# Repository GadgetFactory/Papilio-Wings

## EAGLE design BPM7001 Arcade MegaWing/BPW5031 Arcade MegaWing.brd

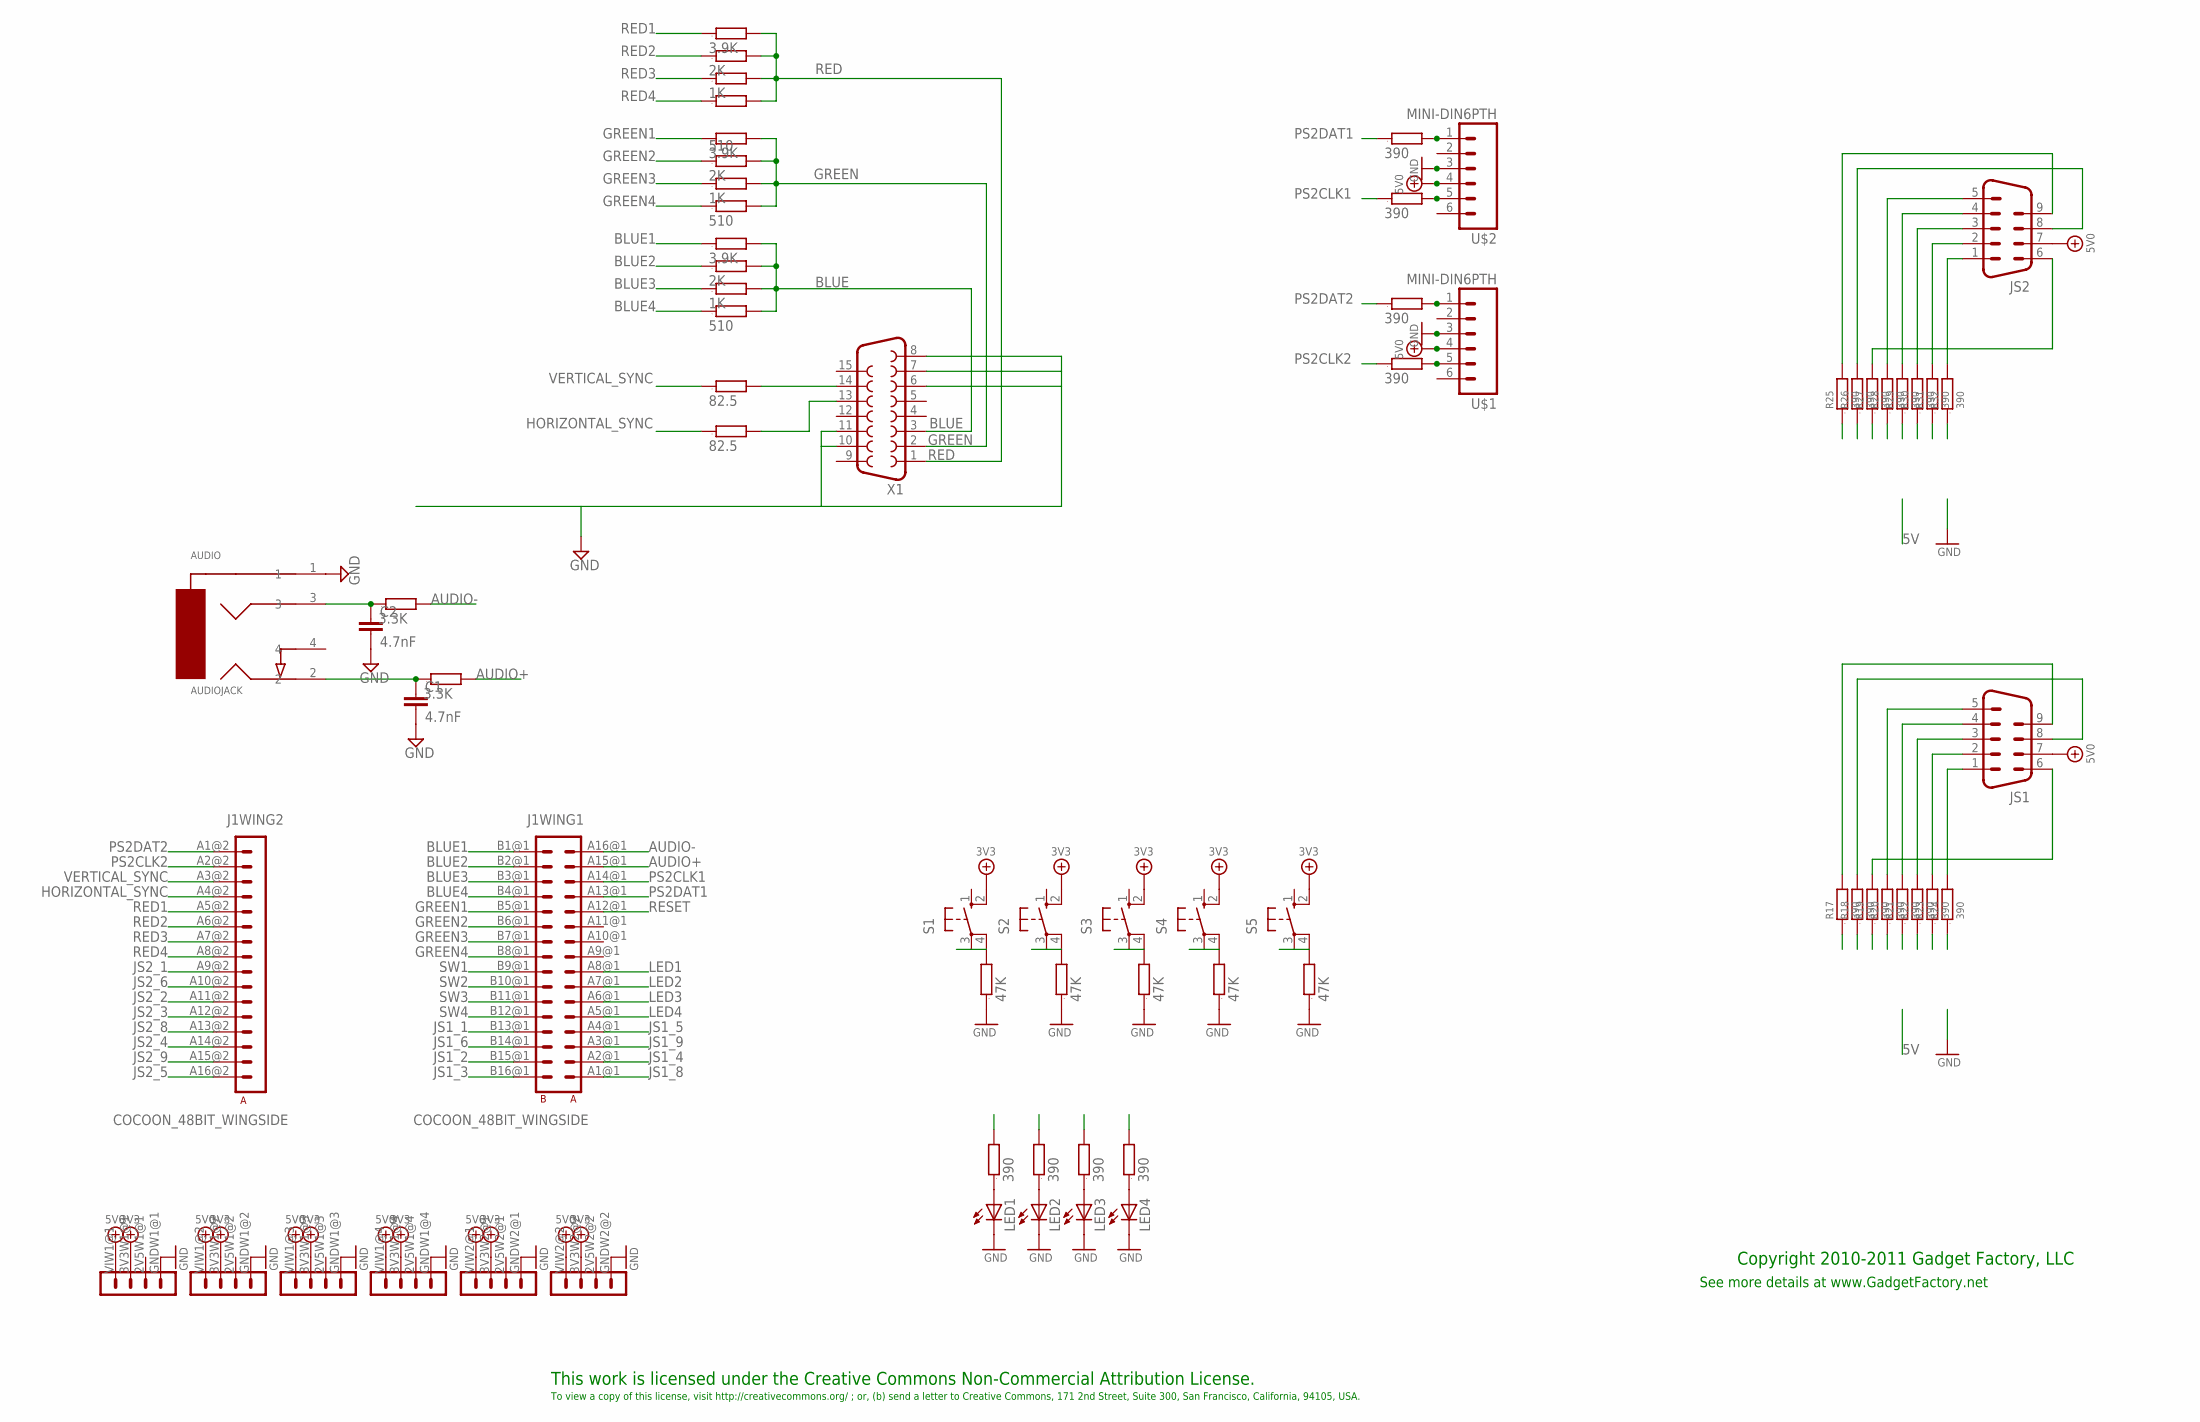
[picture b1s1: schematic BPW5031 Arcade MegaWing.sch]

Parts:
AUDIO: AUDIOJACK; AUDJCK
C1, C2: 4.7nF; C050-025X075
J1: COCOON_48BIT_WINGSIDE
JS1, JS2: M09HP
LED1, LED2, LED3, LED4: LEDCHIPLED_0603; CHIPLED_0603
LOGO2: BUTTERFLY_LOGO
R1, R2, R3: 3.9K; 0603
R4, R5: 82.5; 0603
R6, R7, R8: 2K; 0603
R9, R11, R13: 1K; 0603
R10, R12, R14: 510; 0603
R15, R16: 3.3K; 0603
R17, R18, R19, R20, R21, R22, R23, R24, R25, R26, R27, R28, R29, R30, R31, R32, R37, R38, R39, R40, R42, R43, R44, R45: 390; 0603
R33, R34, R35, R36, R41: 47K; 0603
S1, S2, S3, S4, S5: 10-XX; B3F-10XX
U$1, U$2: MINI-DIN6PTH; MINI-DIN6
X1: F15HDH; HDF15H

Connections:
3V3: J1.3V3W1@1 (3V3), J1.3V3W1@2 (3V3), J1.3V3W1@3 (3V3), J1.3V3W1@4 (3V3), J1.3V3W2@1 (3V3), J1.3V3W2@2 (3V3), S1.2 (S1), S2.2 (S1), S3.2 (S1), S4.2 (S1), S5.2 (S1)
5V0: J1.VIW1@1 (5V), J1.VIW1@2 (5V), J1.VIW1@3 (5V), J1.VIW1@4 (5V), J1.VIW2@1 (5V), J1.VIW2@2 (5V), JS1.7, JS2.7, U$1.4, U$2.4
AUDIO+: J1.A15@1 (A15), R16.2
AUDIO-: J1.A16@1 (A16), R15.2
BLUE: R3.2, R8.2, R13.2, R14.2, X1.3
BLUE1: J1.B1@1 (B1), R3.1
BLUE2: J1.B2@1 (B2), R8.1
BLUE3: J1.B3@1 (B3), R13.1
BLUE4: J1.B4@1 (B4), R14.1
GND: AUDIO.1, C1.2, C2.2, J1.GNDW1@1 (GND), J1.GNDW1@2 (GND), J1.GNDW1@3 (GND), J1.GNDW1@4 (GND), J1.GNDW2@1 (GND), J1.GNDW2@2 (GND), LED1.C, LED2.C, LED3.C, LED4.C, R33.1, R34.1, R35.1, R36.1, R41.1, U$1.3, U$2.3, X1.6, X1.7, X1.8, X1.10, X1.11
GREEN: R2.2, R7.2, R11.2, R12.2, X1.2
GREEN1: J1.B5@1 (B5), R2.1
GREEN2: J1.B6@1 (B6), R7.1
GREEN3: J1.B7@1 (B7), R11.1
GREEN4: J1.B8@1 (B8), R12.1
HORIZONTAL_SYNC: J1.A4@2 (A4), R4.1
JS1_1: J1.B13@1 (B13), R32.1
JS1_2: J1.B15@1 (B15), R31.1
JS1_3: J1.B16@1 (B16), R30.1
JS1_4: J1.A2@1 (A2), R29.1
JS1_5: J1.A4@1 (A4), R28.1
JS1_6: J1.B14@1 (B14), R27.1
JS1_8: J1.A1@1 (A1), R26.1
JS1_9: J1.A3@1 (A3), R25.1
JS2_1: J1.A9@2 (A9), R24.1
JS2_2: J1.A11@2 (A11), R23.1
JS2_3: J1.A12@2 (A12), R22.1
JS2_4: J1.A14@2 (A14), R21.1
JS2_5: J1.A16@2 (A16), R20.1
JS2_6: J1.A10@2 (A10), R19.1
JS2_8: J1.A13@2 (A13), R18.1
JS2_9: J1.A15@2 (A15), R17.1
LED1: J1.A8@1 (A8), R37.2
LED2: J1.A7@1 (A7), R38.2
LED3: J1.A6@1 (A6), R39.2
LED4: J1.A5@1 (A5), R40.2
unnamed: AUDIO.3, C2.1, R15.1
unnamed: LED1.A, R37.1
unnamed: R4.2, X1.13
unnamed: R5.2, X1.14
unnamed: AUDIO.2, C1.1, R16.1
unnamed: LED2.A, R38.1
unnamed: LED3.A, R39.1
unnamed: LED4.A, R40.1
unnamed: R42.2, U$2.1
unnamed: R43.2, U$2.5
unnamed: R44.2, U$1.1
unnamed: R45.2, U$1.5
unnamed: JS2.1, R32.2
unnamed: JS2.2, R31.2
unnamed: JS2.3, R30.2
unnamed: JS2.4, R29.2
unnamed: JS2.5, R28.2
unnamed: JS2.9, R25.2
unnamed: JS2.6, R27.2
unnamed: JS2.8, R26.2
unnamed: JS1.1, R24.2
unnamed: JS1.2, R23.2
unnamed: JS1.3, R22.2
unnamed: JS1.4, R21.2
unnamed: JS1.5, R20.2
unnamed: JS1.9, R17.2
unnamed: JS1.6, R19.2
unnamed: JS1.8, R18.2
PS2CLK1: J1.A14@1 (A14), R43.1
PS2CLK2: J1.A2@2 (A2), R45.1
PS2DAT1: J1.A13@1 (A13), R42.1
PS2DAT2: J1.A1@2 (A1), R44.1
RED: R1.2, R6.2, R9.2, R10.2, X1.1
RED1: J1.A5@2 (A5), R1.1
RED2: J1.A6@2 (A6), R6.1
RED3: J1.A7@2 (A7), R9.1
RED4: J1.A8@2 (A8), R10.1
RESET: J1.A12@1 (A12), R41.2, S5.3, S5.4 (P1)
SW1: J1.B9@1 (B9), R33.2, S1.3, S1.4 (P1)
SW2: J1.B10@1 (B10), R34.2, S2.3, S2.4 (P1)
SW3: J1.B11@1 (B11), R35.2, S3.3, S3.4 (P1)
SW4: J1.B12@1 (B12), R36.2, S4.3, S4.4 (P1)
VERTICAL_SYNC: J1.A3@2 (A3), R5.1

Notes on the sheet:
This work is licensed under the Creative Commons Non-Commercial Attribution License.
To view a copy of this license, visit http://creativecommons.org/ ; or, (b) send a letter to Creative Commons, 171 2nd Street, Suite 300, San Francisco, California, 94105, USA.
Copyright 2010-2011 Gadget Factory, LLC
See more details at www.GadgetFactory.net

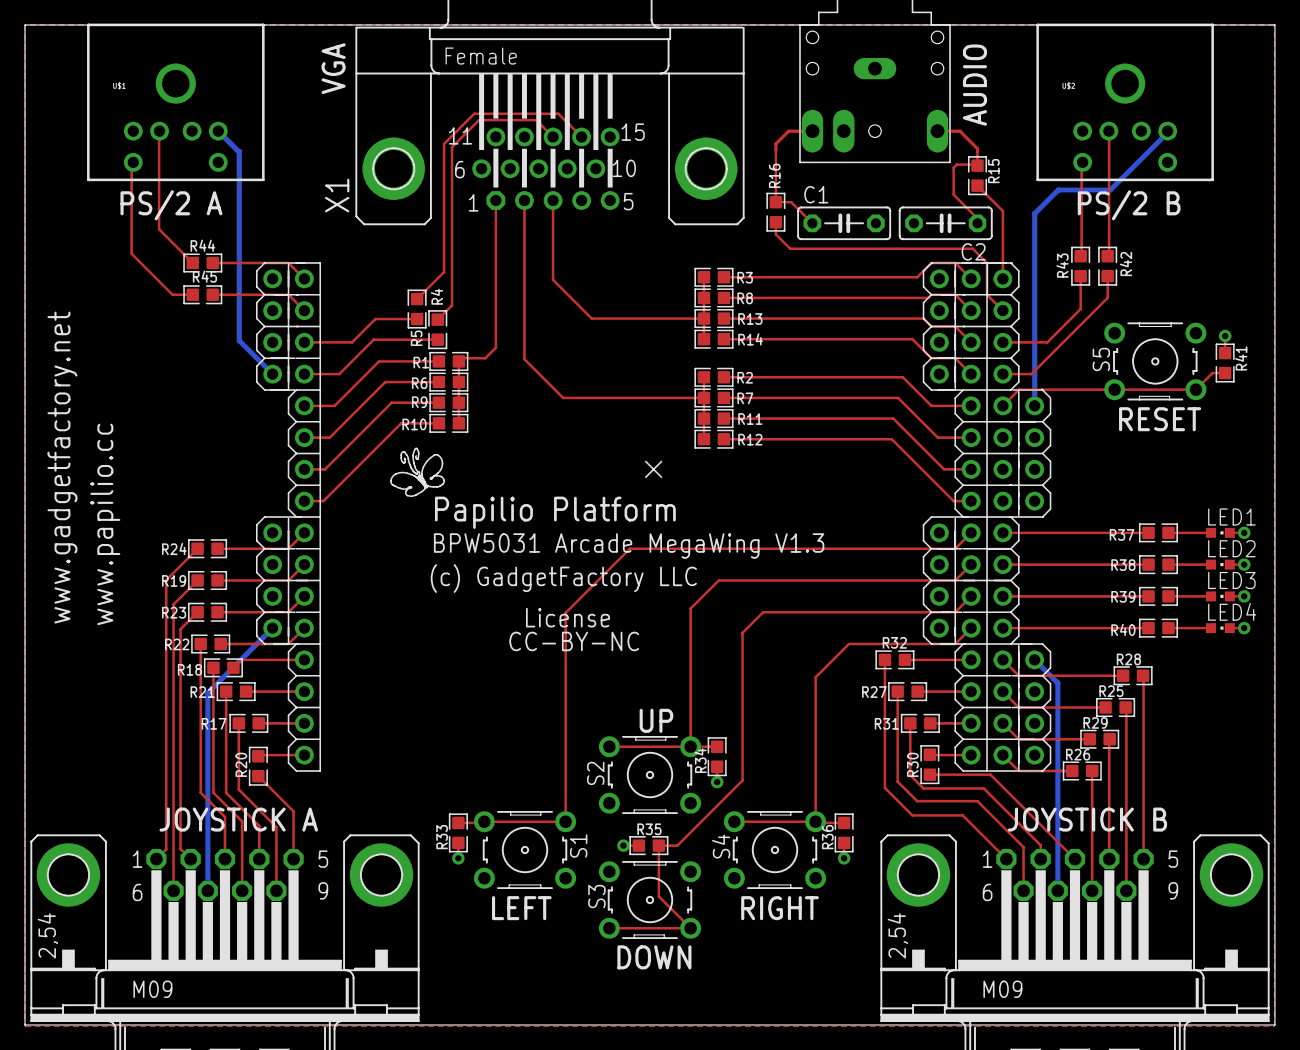
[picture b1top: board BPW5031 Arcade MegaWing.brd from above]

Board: 2 copper layers, 100.0 x 80.0 mm, 64 parts (0 on the bottom side), 79 nets.

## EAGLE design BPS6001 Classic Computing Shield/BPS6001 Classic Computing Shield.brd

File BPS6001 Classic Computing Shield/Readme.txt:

BPS6001 Computing Shield Manufacturing Package - Current Version 1.01

Special assembly instructions:
	-Use RED for the PCB color.
	-All Arduino Mega Header pins should be populated with Male headers on the bottom of the board.
	-There is a V-Score indicated on the dimension layer of this PCB. The board should be manufactured as a single PCB with both sides of the V-Score connected. The end user will snap away the V-Score if they wish to do so.

Partial DigiKey BOM Link (Seeed and Generic Parts not included):
	https://www.digikey.com/classic/RegisteredUser/BOMBillOfMaterials.aspx?path=1&exist=1&id=1859538

Test Plan Home Page:
	http://www.gadgetfactory.net/opmanuals/index.php?n=Main.ComputingShield

CHANGELOG
11/18/2014	Version 1.02
	-Fixed the location of audio jack's.

10/20/2014	Version 1.01
	-Fixed the PS/2 footprints
	-Rotated the whole design 180 degrees to put the connectors at the top of the board and easier to work with.
	-Added Get Started URL

7/30/2014 Version 1.0
	First release with V-Score.

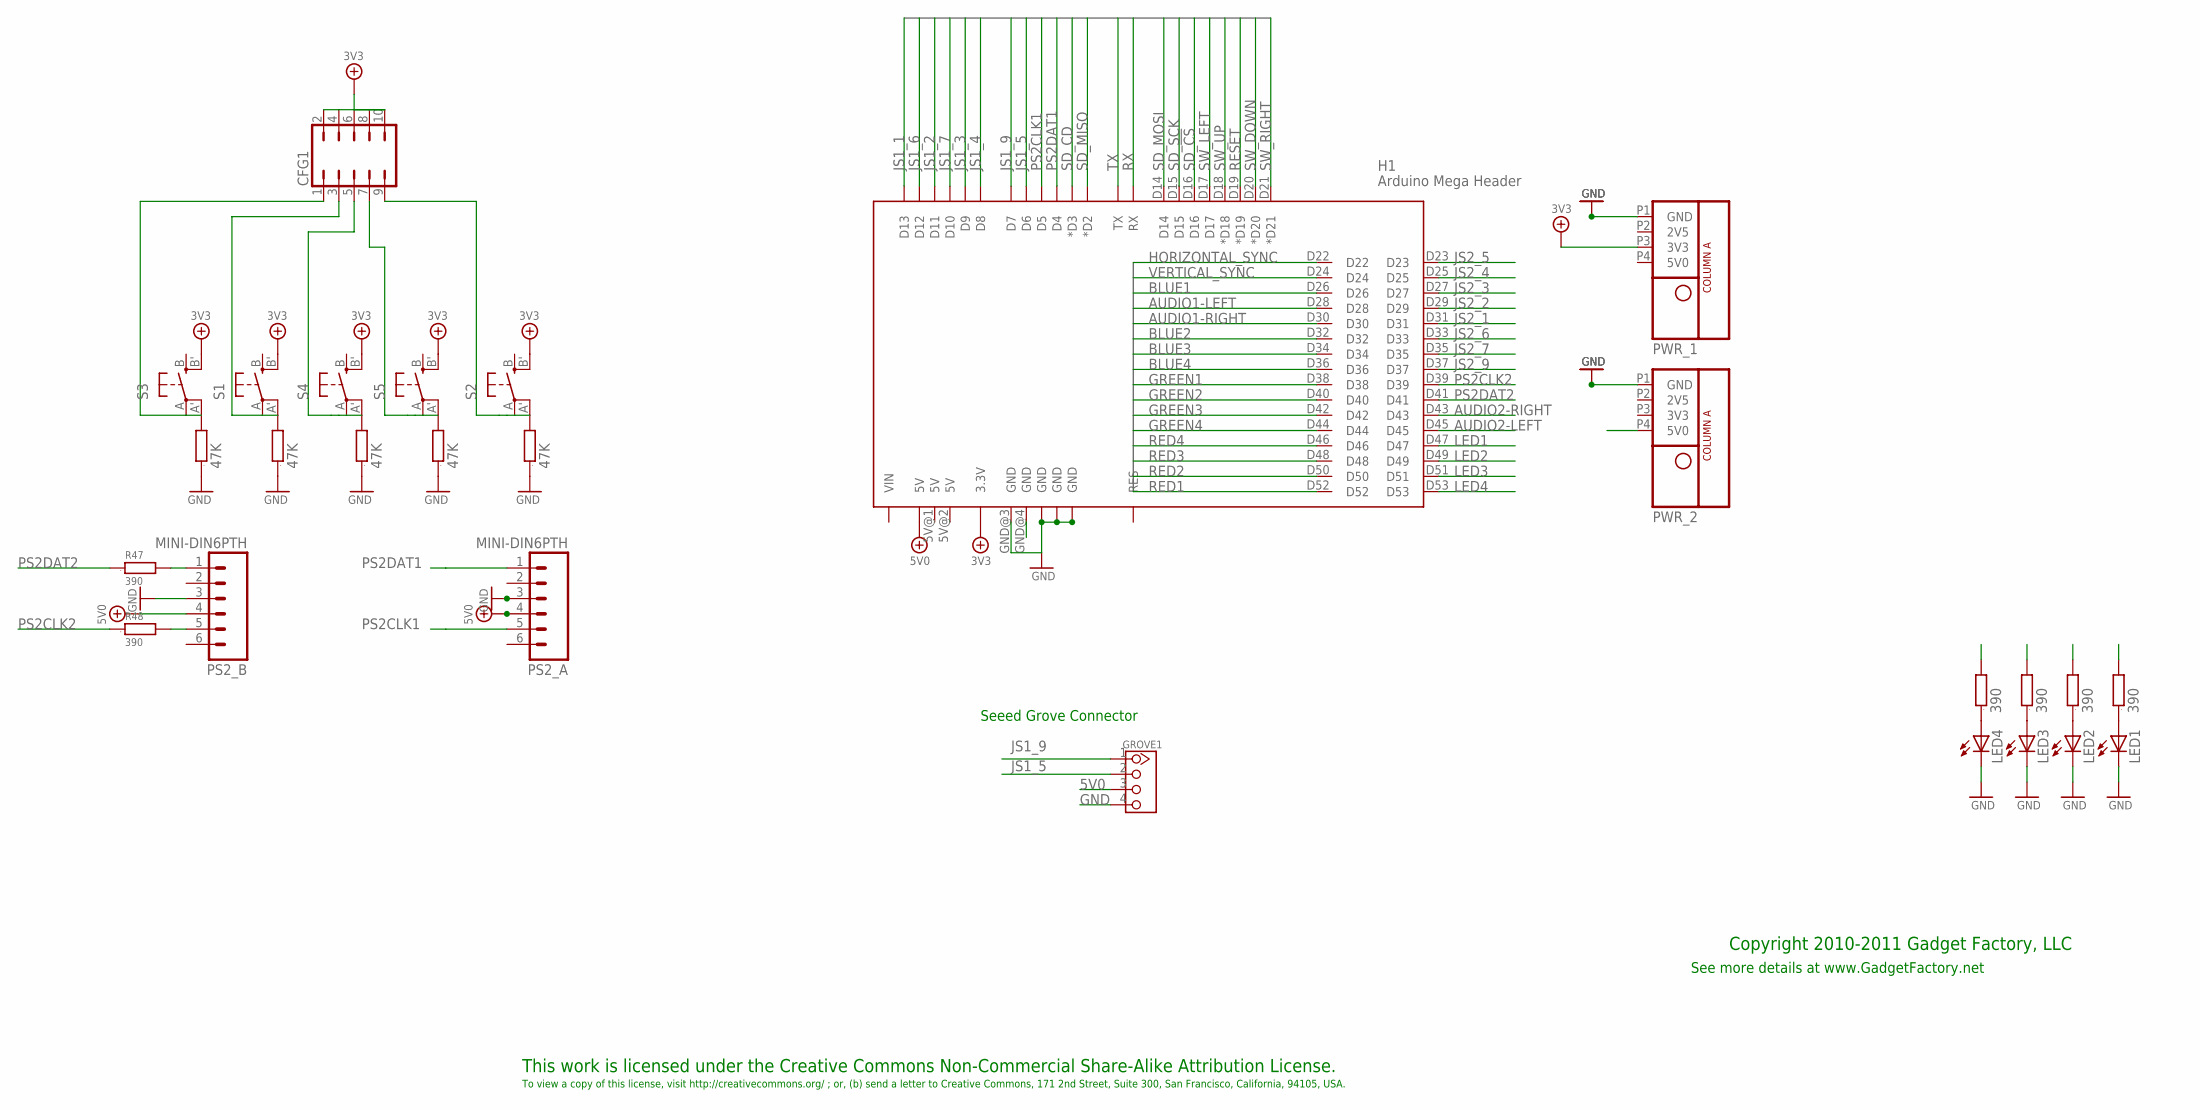
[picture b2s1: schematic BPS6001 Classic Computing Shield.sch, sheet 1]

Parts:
CFG1: JP5Q; PARTNO M20-9720545
GROVE1: CONNECTOR_TWIG-2.0-LEADED; CONNECTOR_4P-LEADED-2.0; PARTNO ACC39145O
H1: Arduino Mega Header; AMEGA_SHIELD_NOANALOG; PARTNO Arduino_Mega_Header
LED1, LED2, LED3, LED4: LEDCHIPLED_0603; CHIPLED_0603; PARTNO LTST-C190GKT
LOGO1: BUTTERFLY_LOGO
PS2_A, PS2_B: MINI-DIN6PTH; MINI-DIN6
PWR_1, PWR_2: POWER_ONLYNOTEXT; POWER_NO_TEXT
R9, R10, R11, R17, R18: 47K; 0603; PARTNO RMCF0603JT47K0
R26, R27, R43, R44, R47, R48: 390; 0603; PARTNO RMCF0603JT390R
S1, S2, S3, S4, S5: EVQQ2; EVQ-Q2; PARTNO PTS525SM10SMTR LFS

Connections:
3V3: CFG1.2, CFG1.4, CFG1.6, CFG1.8, CFG1.10, H1.3.3V, S1.B' (S1), S2.B' (S1), S3.B' (S1), S4.B' (S1), S5.B' (S1); also elsewhere on the board
5V0: GROVE1.3, H1.5V@0 (5V), PS2_A.4
5V0_PS2: PS2_B.4, PWR_2.P4 (5V0)
AUDIO1-LEFT: H1.D28; also elsewhere on the board
AUDIO1-RIGHT: H1.D30; also elsewhere on the board
AUDIO2-LEFT: H1.D45; also elsewhere on the board
AUDIO2-RIGHT: H1.D43; also elsewhere on the board
BLUE1: H1.D26; also elsewhere on the board
BLUE2: H1.D32; also elsewhere on the board
BLUE3: H1.D34; also elsewhere on the board
BLUE4: H1.D36; also elsewhere on the board
GND: GROVE1.4, H1.GND@0 (GND), H1.GND@1 (GND), H1.GND@2 (GND), H1.GND@3 (GND), PS2_A.3, R9.1, R10.1, R11.1, R17.1, R18.1; also elsewhere on the board
GREEN1: H1.D38; also elsewhere on the board
GREEN2: H1.D40; also elsewhere on the board
GREEN3: H1.D42; also elsewhere on the board
GREEN4: H1.D44; also elsewhere on the board
HORIZONTAL_SYNC: H1.D22; also elsewhere on the board
JOY_3V3: PWR_1.P3 (3V3); also elsewhere on the board
JOY_GND: H1.GND@4 (GND), LED1.C, LED2.C, LED3.C, LED4.C, PS2_B.3, PWR_1.P1 (GND), PWR_2.P1 (GND); also elsewhere on the board
JS1_1: H1.D13; also elsewhere on the board
JS1_2: H1.D11; also elsewhere on the board
JS1_3: H1.D9; also elsewhere on the board
JS1_4: H1.D8; also elsewhere on the board
JS1_5: GROVE1.2, H1.D6; also elsewhere on the board
JS1_6: H1.D12; also elsewhere on the board
JS1_7: H1.D10; also elsewhere on the board
JS1_9: GROVE1.1, H1.D7; also elsewhere on the board
JS2_1: H1.D31; also elsewhere on the board
JS2_2: H1.D29; also elsewhere on the board
JS2_3: H1.D27; also elsewhere on the board
JS2_4: H1.D25; also elsewhere on the board
JS2_5: H1.D23; also elsewhere on the board
JS2_6: H1.D33; also elsewhere on the board
JS2_7: H1.D35; also elsewhere on the board
JS2_9: H1.D37; also elsewhere on the board
LED1: H1.D47, R26.2
LED2: H1.D49, R27.2
LED3: H1.D51, R43.2
LED4: H1.D53, R44.2
unnamed: LED4.A, R44.1
unnamed: LED3.A, R43.1
unnamed: LED2.A, R27.1
unnamed: LED1.A, R26.1
unnamed: PS2_B.1, R47.2
unnamed: PS2_B.5, R48.2
PS2CLK1: H1.D5, PS2_A.5
PS2CLK2: H1.D39, R48.1
PS2DAT1: H1.D4, PS2_A.1
PS2DAT2: H1.D41, R47.1
RED1: H1.D52; also elsewhere on the board
RED2: H1.D50; also elsewhere on the board
RED3: H1.D48; also elsewhere on the board
RED4: H1.D46; also elsewhere on the board
RESET: CFG1.9, H1.D19 (*D19), R11.2, S2.A, S2.A' (P1)
RX: H1.RX; also elsewhere on the board
SD_!CS: H1.D16; also elsewhere on the board
SD_CD: H1.D3 (*D3); also elsewhere on the board
SD_MISO: H1.D2 (*D2); also elsewhere on the board
SD_MOSI: H1.D14; also elsewhere on the board
SD_SCK: H1.D15; also elsewhere on the board
SW_DOWN: CFG1.5, H1.D20 (*D20), R17.2, S4.A, S4.A' (P1)
SW_LEFT: CFG1.1, H1.D17, R9.2, S3.A, S3.A' (P1)
SW_RIGHT: CFG1.7, H1.D21 (*D21), R18.2, S5.A, S5.A' (P1)
SW_UP: CFG1.3, H1.D18 (*D18), R10.2, S1.A, S1.A' (P1)
TX: H1.TX; also elsewhere on the board
VERTICAL_SYNC: H1.D24; also elsewhere on the board

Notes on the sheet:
This work is licensed under the Creative Commons Non-Commercial Share-Alike Attribution License.
To view a copy of this license, visit http://creativecommons.org/ ; or, (b) send a letter to Creative Commons, 171 2nd Street, Suite 300, San Francisco, California, 94105, USA.
Copyright 2010-2011 Gadget Factory, LLC
See more details at www.GadgetFactory.net
Seeed Grove Connector

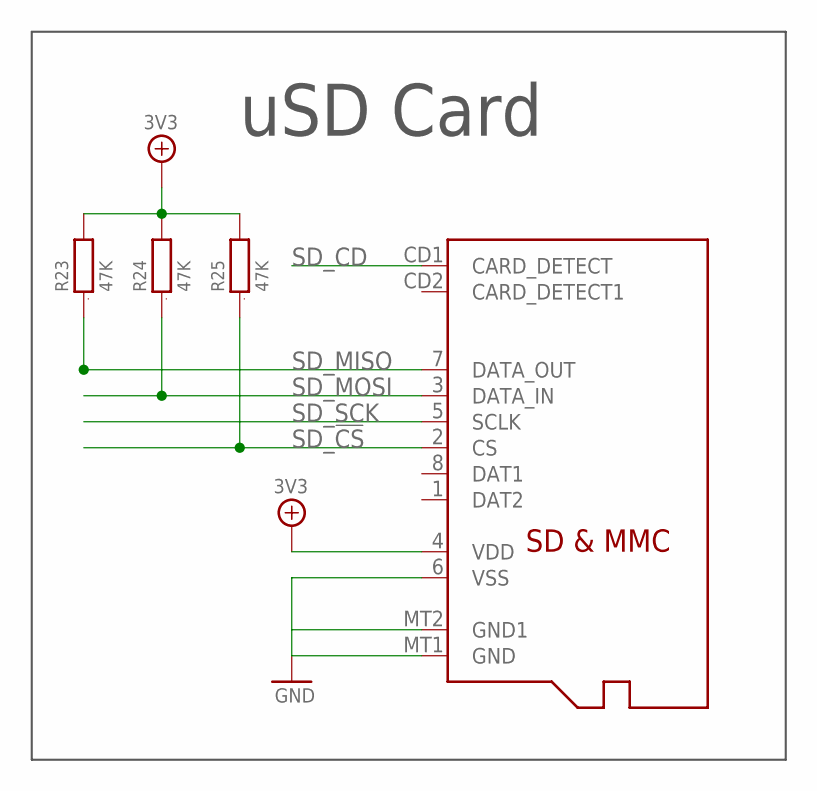
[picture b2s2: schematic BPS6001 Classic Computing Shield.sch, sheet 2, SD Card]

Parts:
R23, R24, R25: 47K; 0603; PARTNO RMCF0603JT47K0
SD1: MICROSD; PARTNO 101-00660-68-6

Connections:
3V3: R23.2, R24.2, R25.2, SD1.4 (VDD); also elsewhere on the board
GND: SD1.6 (VSS), SD1.MT1 (GND), SD1.MT2 (GND1); also elsewhere on the board
SD_!CS: R25.1, SD1.2 (CS); also elsewhere on the board
SD_CD: SD1.CD1 (CARD_DETECT); also elsewhere on the board
SD_MISO: R23.1, SD1.7 (DATA_OUT); also elsewhere on the board
SD_MOSI: R24.1, SD1.3 (DATA_IN); also elsewhere on the board
SD_SCK: SD1.5 (SCLK); also elsewhere on the board

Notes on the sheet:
uSD Card

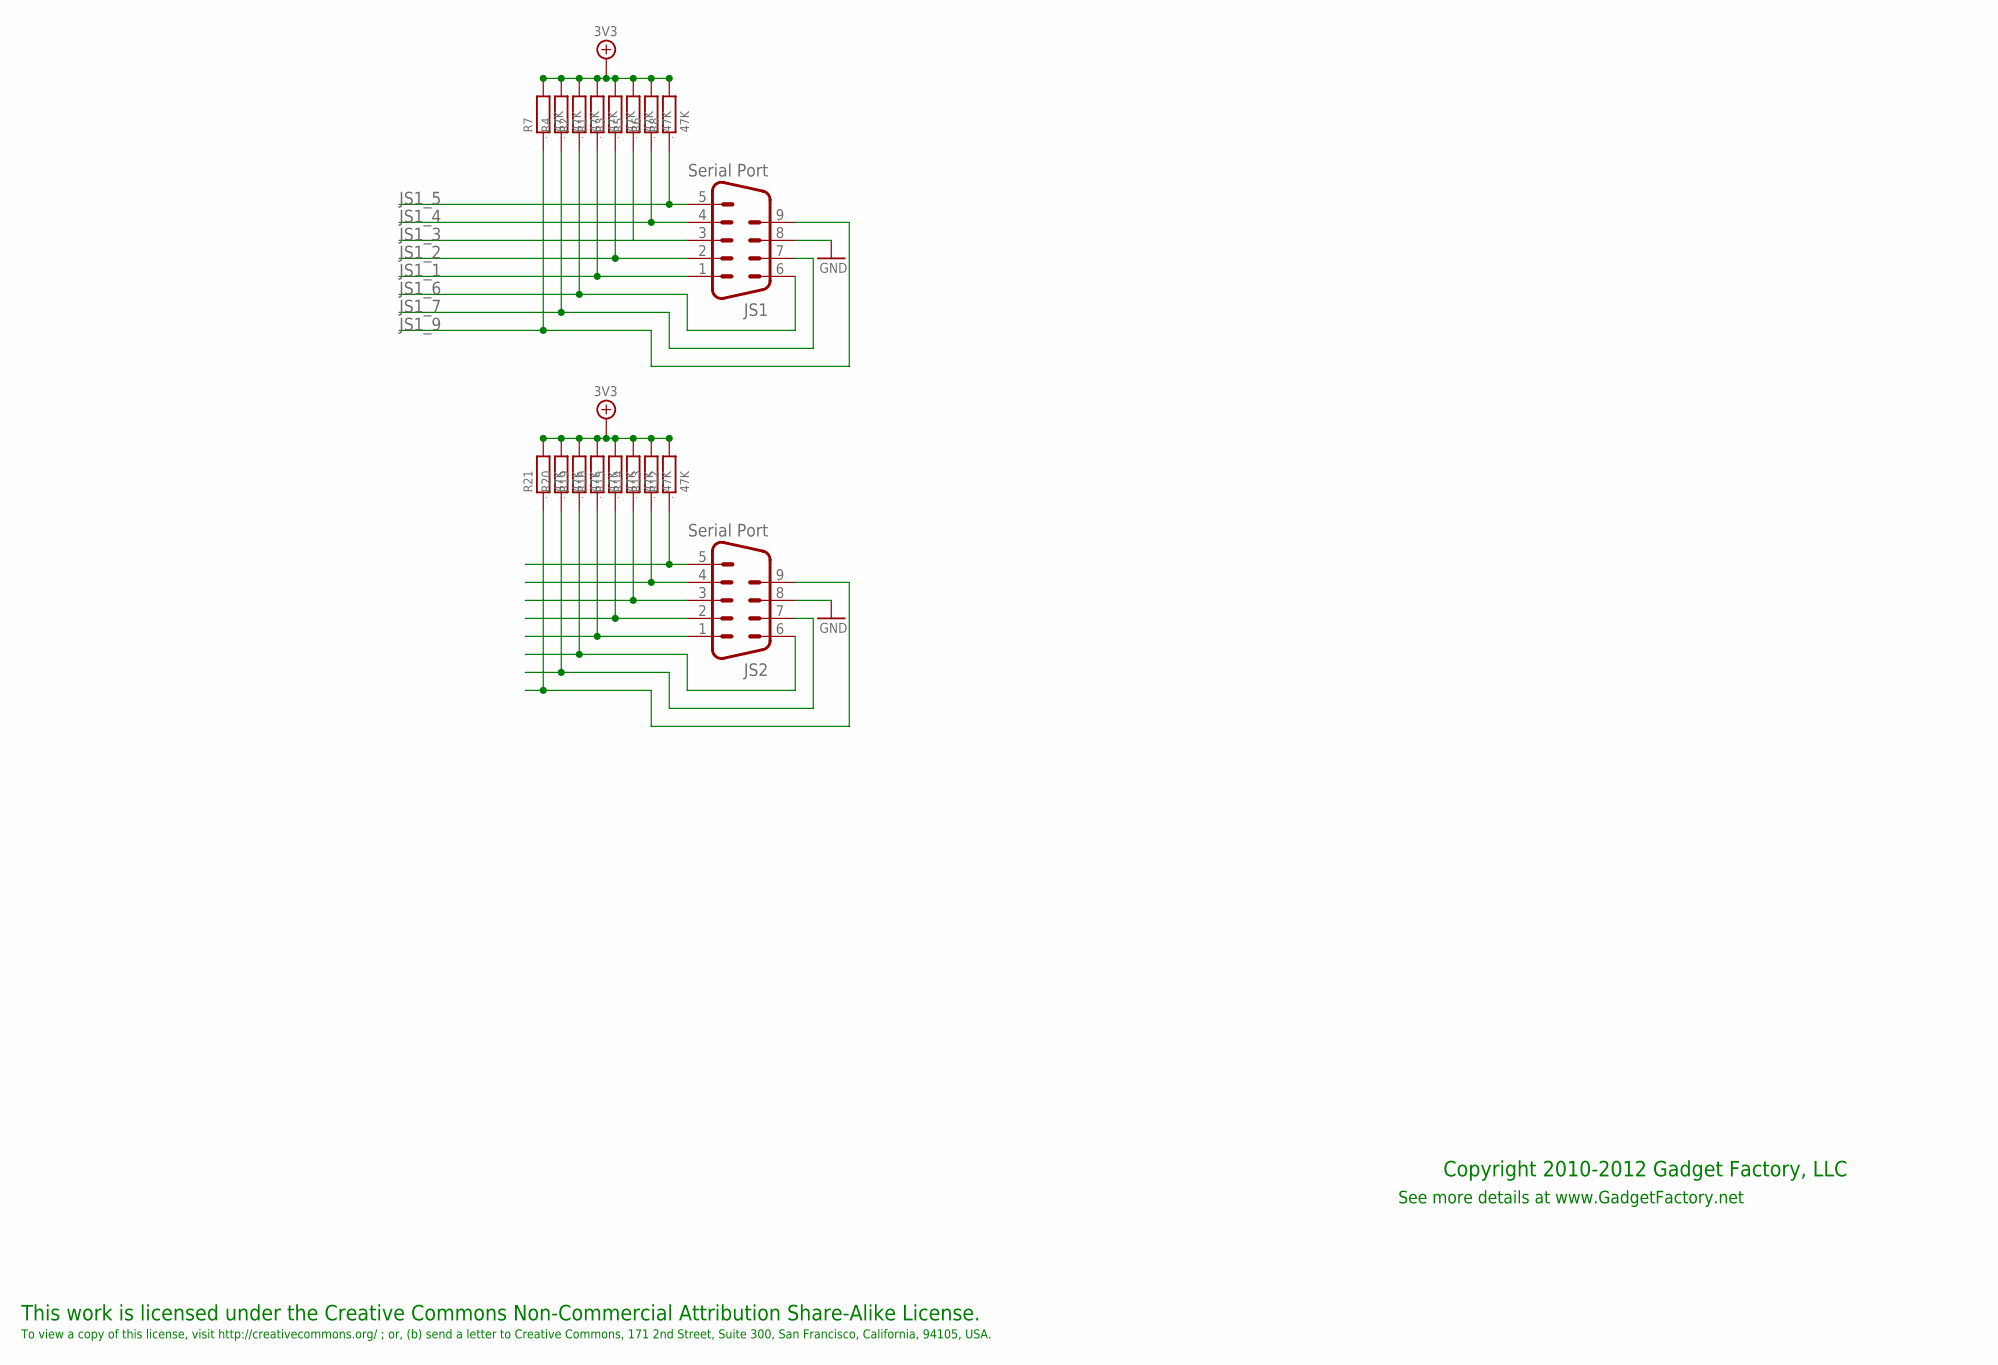
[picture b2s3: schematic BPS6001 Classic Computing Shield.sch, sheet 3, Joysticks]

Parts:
JS1, JS2: Serial Port; M09HP; PARTNO 10090097-P094VLF
R1, R2, R3, R4, R5, R6, R7, R8, R12, R13, R14, R15, R16, R19, R20, R21: 47K; 0603; PARTNO RMCF0603JT47K0

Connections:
3V3: R1.2, R2.2, R3.2, R4.2, R5.2, R6.2, R7.2, R8.2; also elsewhere on the board
GND: JS1.8; also elsewhere on the board
JOY_3V3: R12.2, R13.2, R14.2, R15.2, R16.2, R19.2, R20.2, R21.2; also elsewhere on the board
JOY_GND: JS2.8; also elsewhere on the board
JS1_1: JS1.1, R1.1; also elsewhere on the board
JS1_2: JS1.2, R3.1; also elsewhere on the board
JS1_3: JS1.3, R5.1; also elsewhere on the board
JS1_4: JS1.4, R6.1; also elsewhere on the board
JS1_5: JS1.5, R8.1; also elsewhere on the board
JS1_6: JS1.6, R2.1; also elsewhere on the board
JS1_7: JS1.7, R4.1; also elsewhere on the board
JS1_9: JS1.9, R7.1; also elsewhere on the board
JS2_1: JS2.1, R16.1; also elsewhere on the board
JS2_2: JS2.2, R15.1; also elsewhere on the board
JS2_3: JS2.3, R14.1; also elsewhere on the board
JS2_4: JS2.4, R13.1; also elsewhere on the board
JS2_5: JS2.5, R12.1; also elsewhere on the board
JS2_6: JS2.6, R19.1; also elsewhere on the board
JS2_7: JS2.7, R20.1; also elsewhere on the board
JS2_9: JS2.9, R21.1; also elsewhere on the board

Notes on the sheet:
This work is licensed under the Creative Commons Non-Commercial Attribution Share-Alike License.
To view a copy of this license, visit http://creativecommons.org/ ; or, (b) send a letter to Creative Commons, 171 2nd Street, Suite 300, San Francisco, California, 94105, USA.
Copyright 2010-2012 Gadget Factory, LLC
See more details at www.GadgetFactory.net

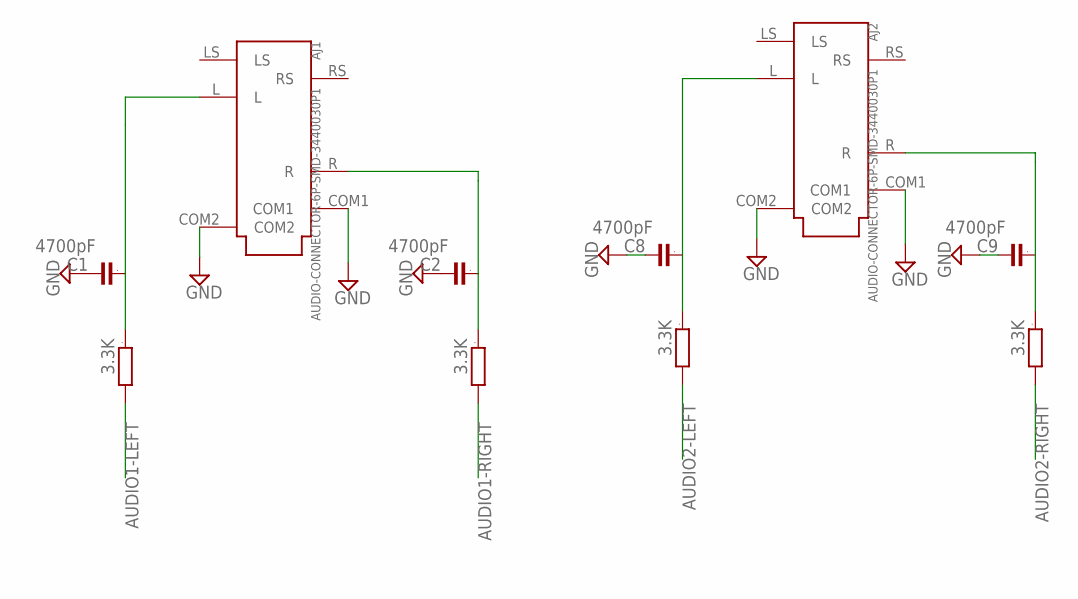
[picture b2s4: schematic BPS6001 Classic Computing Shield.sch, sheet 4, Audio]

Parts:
AJ1, AJ2: AUDIO-CONNECTOR-6P-SMD-3440030P1; 6P-SMD-3.5; PARTNO 3440030P1
C1, C2, C8, C9: 4700pF; 0603; PARTNO C0603C472J5RACTU
R22, R28, R45, R46: 3.3K; 0603; PARTNO RMCF0603JT3K30

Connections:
AUDIO1-LEFT: R22.2; also elsewhere on the board
AUDIO1-RIGHT: R28.2; also elsewhere on the board
AUDIO2-LEFT: R45.2; also elsewhere on the board
AUDIO2-RIGHT: R46.2; also elsewhere on the board
GND: AJ1.COM1, AJ1.COM2, C1.2, C2.2; also elsewhere on the board
JOY_GND: AJ2.COM1, AJ2.COM2, C8.2, C9.2; also elsewhere on the board
unnamed: AJ2.L, C8.1, R45.1
unnamed: AJ1.L, C1.1, R22.1
unnamed: AJ2.R, C9.1, R46.1
unnamed: AJ1.R, C2.1, R28.1

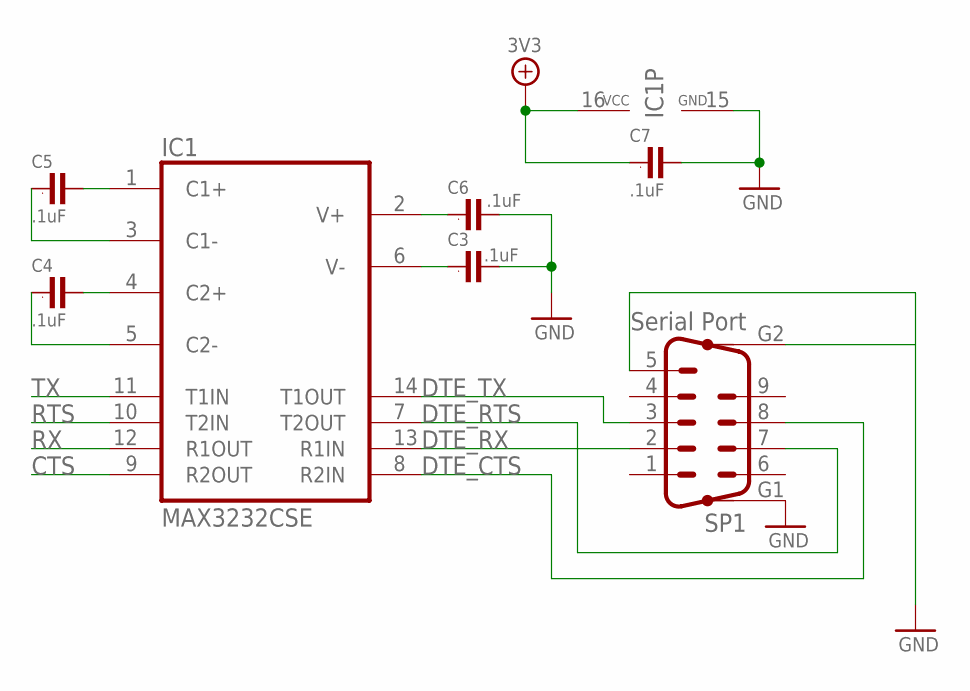
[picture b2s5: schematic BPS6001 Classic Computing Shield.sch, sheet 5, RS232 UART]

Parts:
C3, C4, C5, C6, C7: .1uF; 0805; PARTNO GRM21BR71E104KA01L
IC1: MAX3232CSE; SO16; PARTNO MAX3232ECDR
SP1: Serial Port; M09HP; PARTNO 10090097-P094VLF

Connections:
3V3: C7.1, IC1.16 (VCC); also elsewhere on the board
CTS: IC1.9 (R2OUT)
DTE_CTS: IC1.8 (R2IN), SP1.8
DTE_RTS: IC1.7 (T2OUT), SP1.7
DTE_RX: IC1.13 (R1IN), SP1.2
DTE_TX: IC1.14 (T1OUT), SP1.3
GND: C3.2, C6.2, C7.2, IC1.15 (GND), SP1.5, SP1.G1, SP1.G2; also elsewhere on the board
unnamed: C6.1, IC1.2 (V+)
unnamed: C3.1, IC1.6 (V-)
unnamed: C5.2, IC1.1 (C1+)
unnamed: C4.2, IC1.4 (C2+)
unnamed: C5.1, IC1.3 (C1-)
unnamed: C4.1, IC1.5 (C2-)
RTS: IC1.10 (T2IN)
RX: IC1.12 (R1OUT); also elsewhere on the board
TX: IC1.11 (T1IN); also elsewhere on the board

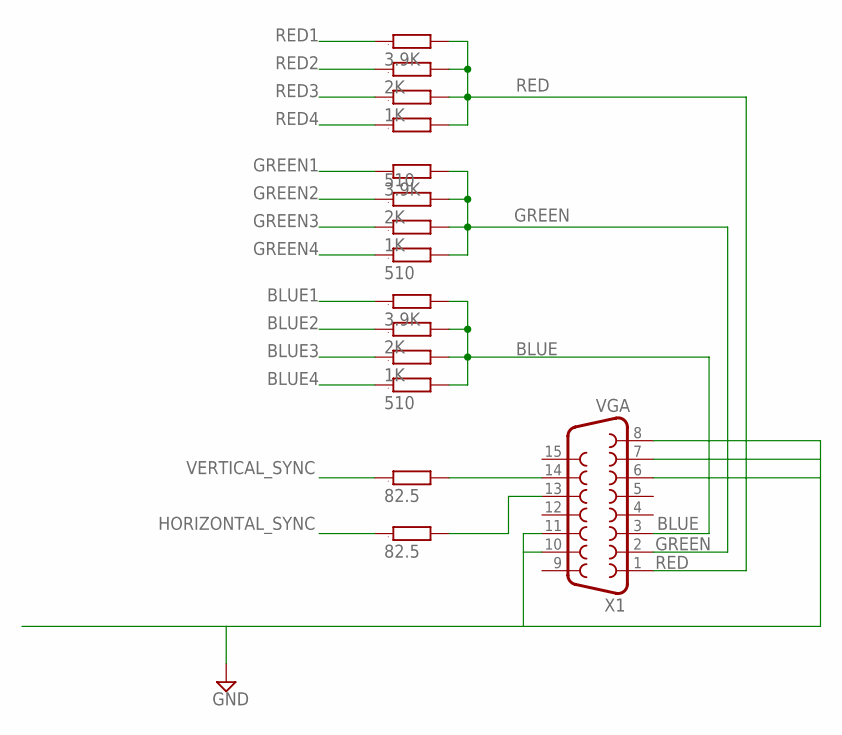
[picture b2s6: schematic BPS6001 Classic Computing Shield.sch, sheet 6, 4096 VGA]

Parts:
R29, R30: 82.5; 0603; PARTNO RMCF0603FT82R5
R31, R35, R42: 3.9K; 0603; PARTNO RMCF0603JT3K90
R32, R36, R41: 2K; 0603; PARTNO RMCF0603JT2K00
R33, R37, R40: 1K; 0603; PARTNO RMCF0603JT1K00
R34, R38, R39: 510; 0603; PARTNO RMCF0603JT510R
X1: VGA; HDF15H; PARTNO 1-1734530-1

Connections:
BLUE: R31.2, R32.2, R33.2, R34.2, X1.3
BLUE1: R31.1; also elsewhere on the board
BLUE2: R32.1; also elsewhere on the board
BLUE3: R33.1; also elsewhere on the board
BLUE4: R34.1; also elsewhere on the board
GND: X1.6, X1.7, X1.8, X1.10, X1.11; also elsewhere on the board
GREEN: R35.2, R36.2, R37.2, R38.2, X1.2
GREEN1: R35.1; also elsewhere on the board
GREEN2: R36.1; also elsewhere on the board
GREEN3: R37.1; also elsewhere on the board
GREEN4: R38.1; also elsewhere on the board
HORIZONTAL_SYNC: R29.1; also elsewhere on the board
unnamed: R29.2, X1.13
unnamed: R30.2, X1.14
RED: R39.2, R40.2, R41.2, R42.2, X1.1
RED1: R42.1; also elsewhere on the board
RED2: R41.1; also elsewhere on the board
RED3: R40.1; also elsewhere on the board
RED4: R39.1; also elsewhere on the board
VERTICAL_SYNC: R30.1; also elsewhere on the board

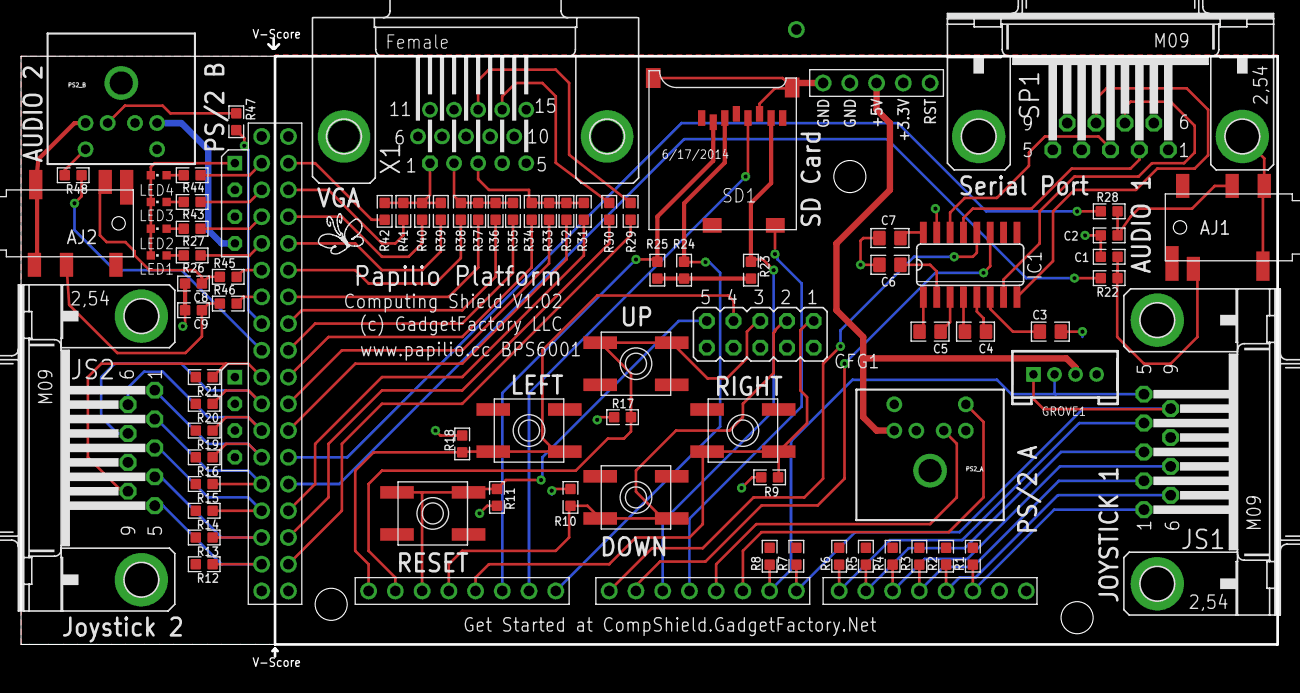
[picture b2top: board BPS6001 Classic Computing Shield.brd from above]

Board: 2 copper layers, 119.3 x 61.1 mm, 85 parts (0 on the bottom side), 85 nets.

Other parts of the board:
U$1, U$2, U$3: STAND-OFF-TIGHT

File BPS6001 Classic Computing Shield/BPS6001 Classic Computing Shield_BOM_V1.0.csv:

Qty-1,Part References,Value,Package,Mfg Part Num,Mfg Name,VID,Vendor Part Num,Description,Pkg Code,XREF
1,"GROVE1",,CONNECTOR_4P-LEADED-2.0,ACC39145O,Seeed Studio,SD,ACC39145O,Seeed Universal Grove Connector,*,REF178
4,"LED1, LED2, LED3, LED4",,CHIPLED_0603,LTST-C190GKT,LITE-ON INC (VA),DK,160-1183-1-ND,LED GREEN CLEAR 0603 SMD,603,REF176
1,"CFG1",,JP5Q,M20-9720545,Harwin,DK,952-1927-ND,2X5POS DIL VERTICAL PIN HEADER,*,REF177
5,"S1, S2, S3, S4, S5",,EVQ-Q2,PTS525SM10SMTR LFS,C&K Components,DK,CKN9104CT-ND,SWITCH TACTILE SPST-NO 0.05A 12V,*,REF119
5,"C3, C4, C5, C6, C7",.1uF,0805,GRM21BR71E104KA01L,MURATA ELECTRONICS (VA),DK,490-1673-1-ND,CAP CER .1UF 25V 10% X7R 0805,805,REF97
3,"R33, R37, R40",1K,0603,RMCF0603JT1K00,StackPole,DK,RMCF0603JT1K00CT-ND,RES 1K OHM 1/10W 5% 0603,603,REF140
3,"R32, R36, R41",2K,0603,RMCF0603JT2K00,Stackpole,DK,RMCF0603JT2K00CT-ND,RES 2K OHM 1/10W 5% 0603,603,REF172
4,"R22, R28, R45, R46",3.3K,0603,RMCF0603JT3K30,Stackpole,DK,RMCF0603JT3K30CT-ND,RES 3.3K OHM 1/10W 5% 0603,603,REF168
3,"R31, R35, R42",3.9K,0603,RMCF0603JT3K90,Stackpole,DK,RMCF0603JT3K90CT-ND,RES 3.9K OHM 1/10W 5% 0603,603,REF171
24,"R1, R2, R3, R4, R5, R6, R7, R8, R9, R10, R11, R12, R13, R14, R15, R16, R17, R18, R19, R20, R21, R23, R24, R25",47K,0603,RMCF0603JT47K0,Stackpole,DK,RMCF0603JT47K0CT-ND,RES 47K OHM 1/10W 5% 0603,603,REF167
2,"R29, R30",82.5,0603,RMCF0603FT82R5,Stackpole,DK,RMCF0603FT82R5CT-ND,RES 82.5 OHM 1/10W 1% 0603,603,REF170
6,"R26, R27, R43, R44, R47, R48",390,0603,RMCF0603JT390R,StackPole,DK,RMCF0603JT390RCT-ND,RES 390 OHM 1/10W 5% 0603,603,REF141
3,"R34, R38, R39",510,0603,RMCF0603JT510R,Stackpole,DK,RMCF0603JT510RCT-ND,RES 510 OHM 1/10W 5% 0603,603,REF174
4,"C1, C2, C8, C9",4700pF,0603,C0603C472J5RACTU,Kemet,DK,399-1088-1-ND,CAP CER 4700PF 50V 5% X7R 0603 - Audio cap,603,REF175
2,"AJ1, AJ2",AUDIO-CONNECTOR-6P-SMD-3440030P1,6P-SMD-3.5,3440030P1,Seeed Studio,SD,3440030P1,6P-SMD-3.5 - Audio Connector,*,REF183
1,"H1",Arduino Mega Header,AMEGA_SHIELD_NOANALOG,Arduino_Mega_Header,Generic,GN,N/A,1x65 Male Pin Header .1,*,REF185
2,"PS2_A, PS2_B",CON_PS/2,PS/2,MD-60S,CUI,DK,CP-2460-ND,CONN MINIDIN RECPT UNSHIELD 6POS - PS/2,*,REF180
1,"IC1",MAX3232CSE,SO16,MAX3232ECDR,Texas Instruments,DK,296-19851-1-ND,IC RS232 3V5.5V 15KVESD 16-SOIC - Max3232,SO16,REF184
1,"SD1",MICROSD,MICROSD,101-00660-68-6,Amphenol,DK,101-00660-68-6-1-ND,CONN MINI MICRO-SD 8PIN PCB GOLD - MicroSD,*,REF181
3,"JS1, JS2, SP1",Serial Port,M09HP,10090097-P094VLF,FCI,DK,609-4003-ND,DSUB R/A US 9POS PIN - Serial Port,*,REF179
1,"X1",VGA,HDF15H,1-1734530-1,TE Connectivity,DK,A35116-ND,CONN HD D-SUB RCPT R/A 15POS - VGA Connector,*,REF182

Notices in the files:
BPM7001 Arcade MegaWing/BPW5031 Arcade MegaWing.brd:
CC-BY-NC
BPW5020-Audio/BPW5020-Audio-Wing.brd:
License: CC-BY-NC
(c) 2012 Gadget Factory
BPW5046-RGB-LED-Panel/BPW5046-RGB-LED-Panel.brd:
(c) 2014 GadgetFactory LLC
parts and their libraries:
SparkFun-Connectors: Licensing: CC v3.0 Share-Alike You are welcome to use this library for commercial purposes.
